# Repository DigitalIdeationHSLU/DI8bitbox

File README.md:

# DI 8bitbox

"DI 8bitbox" - Digital Ideation Musterplatine zum 140 jährigen Bestehen der HSLU

## What is inside this repository?

* PCB EagleCad Files + Gerber production Files
* Firmware (Arduino Code source)
* Shell script to zip Gerber Files
* CAM File for Itead Studio

## Assembly

### Bills of materials

You'll need following parts in order to finish your board.

* 2 x 100R 0805 SMD resistors
* 1 x 1k 0805 SMD resistor
* 1 x SOT23-3 NPN Transistor
* 2 x 1206 LEDs (preferably white, change resistor according to your colour)
* 1 x Atttiny 84 SMD Version
* 1 x Pogopin Sparkfun Connector ([Link](https://www.sparkfun.com/products/11591))
* 1 x optionally a tiny loudspeaker

You can find the exact details in this [BOM](https://github.com/DigitalIdeationHSLU/DI8bitbox/blob/master/documentation/Warenkorb_juin13_0443.xls) Excel sheet.

### Soldering

With little soldering skills, you should be able to finish the board. Please be careful when mounting the LEDs and the Attiny, since orientation is important. See mounting diagram:

## Install

### Flashing Firmware

Attach the Pogo-pin programmer to an Arduino or another AVR ISP-capable programming device. For the wiring see this photo:

Once in place, prepare your Arduino by adding the Attiny to the list of boards. Here's a [HOWTO](http://highlowtech.org/?p=1695).

Make sure the Arduino settings are correct by selecting "Arduino as ISP", the right Board "Attiny84", the right clock frequency "1Mhz" and the right USB port.

Press the Pogo pins gently onto the pads on the bottom side of the board. Again, orientation is important:

Hit the programming button within your Arduino sketch. You should see a succesful File upload in the terminal screen of the Arduino IDE.

### Final preparation

Attach 3-5 Volts DC to the input pins where you'll find the battery icon. Make sure polarity is correct according to +/- signs. Solder the tiny loudspeaker on the other side of the board. You should hear sound coming out immediately.

## Run

Download either this [Android app](https://play.google.com/store/apps/details?id=org.jfedor.morsecode) for capturing sound or the [Morse Talk](https://play.google.com/store/apps/details?id=com.blueta.morsetransmitter&hl=fr) and hold it above one of the LEDs. You should be able to decrypt the message.

## Credits

* Created by Gordan Savičić & Michael Schürmann, Luzern 2017

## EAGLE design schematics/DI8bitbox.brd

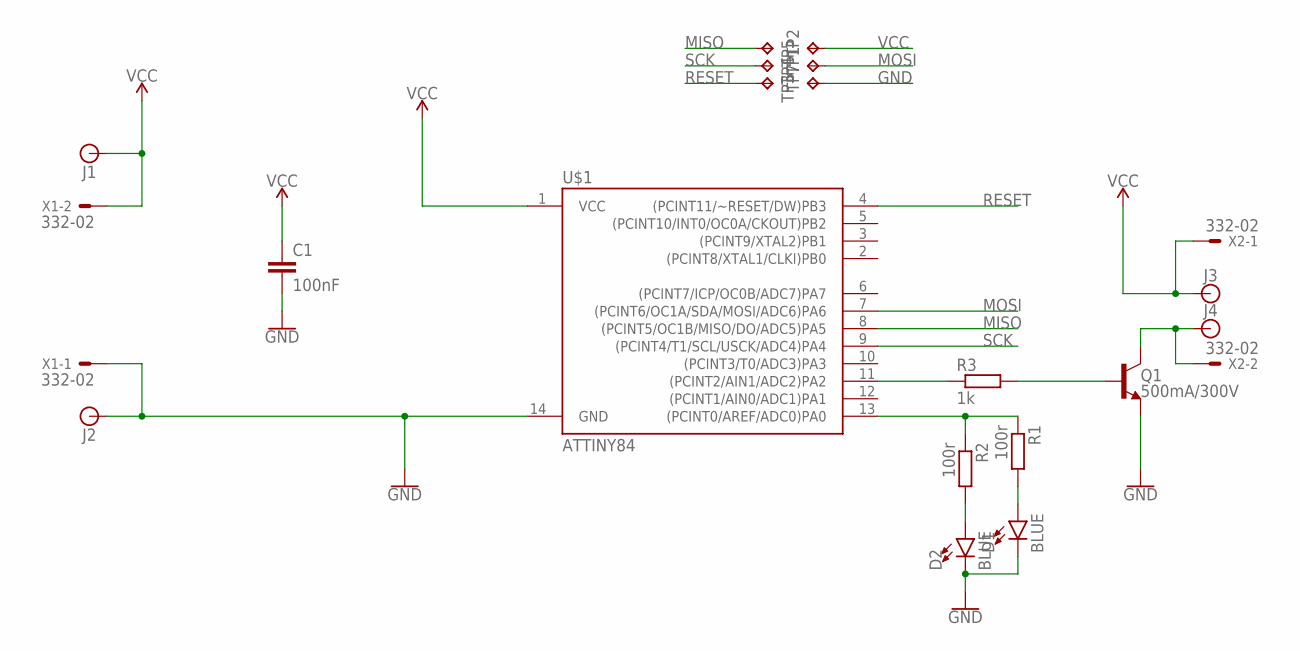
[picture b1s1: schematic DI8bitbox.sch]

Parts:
C1: 100nF; 1206
D1, D2: BLUE; LED-1206
J1, J2, J3, J4: BANANA_CONN
Q1: 500mA/300V; SOT23-3
R1, R2: 100r; M0805
R3: 1k; M0805
TP1, TP2, TP3, TP4, TP5, TP7: TPTP18R; TP18R
U$1: ATTINY84; SO14
X1, X2: 332-02

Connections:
GND: C1.2, D1.C, D2.C, J2.P$1, Q1.2 (E), TP7.TP, U$1.14 (GND), X1.1
MISO: TP5.TP, U$1.8 ((PCINT5/OC1B/MISO/DO/ADC5)PA5)
MOSI: TP1.TP, U$1.7 ((PCINT6/OC1A/SDA/MOSI/ADC6)PA6)
unnamed: R1.1, R2.1, U$1.13 ((PCINT0/AREF/ADC0)PA0)
unnamed: D2.A, R2.2
unnamed: D1.A, R1.2
unnamed: Q1.1 (B), R3.2
unnamed: R3.1, U$1.11 ((PCINT2/AIN1/ADC2)PA2)
RESET: TP3.TP, U$1.4 ((PCINT11/~RESET/DW)PB3)
SCK: TP4.TP, U$1.9 ((PCINT4/T1/SCL/USCK/ADC4)PA4)
SPK: J4.P$1, Q1.3 (C), X2.2
VCC: C1.1, J1.P$1, J3.P$1, TP2.TP, U$1.1 (VCC), X1.2, X2.1

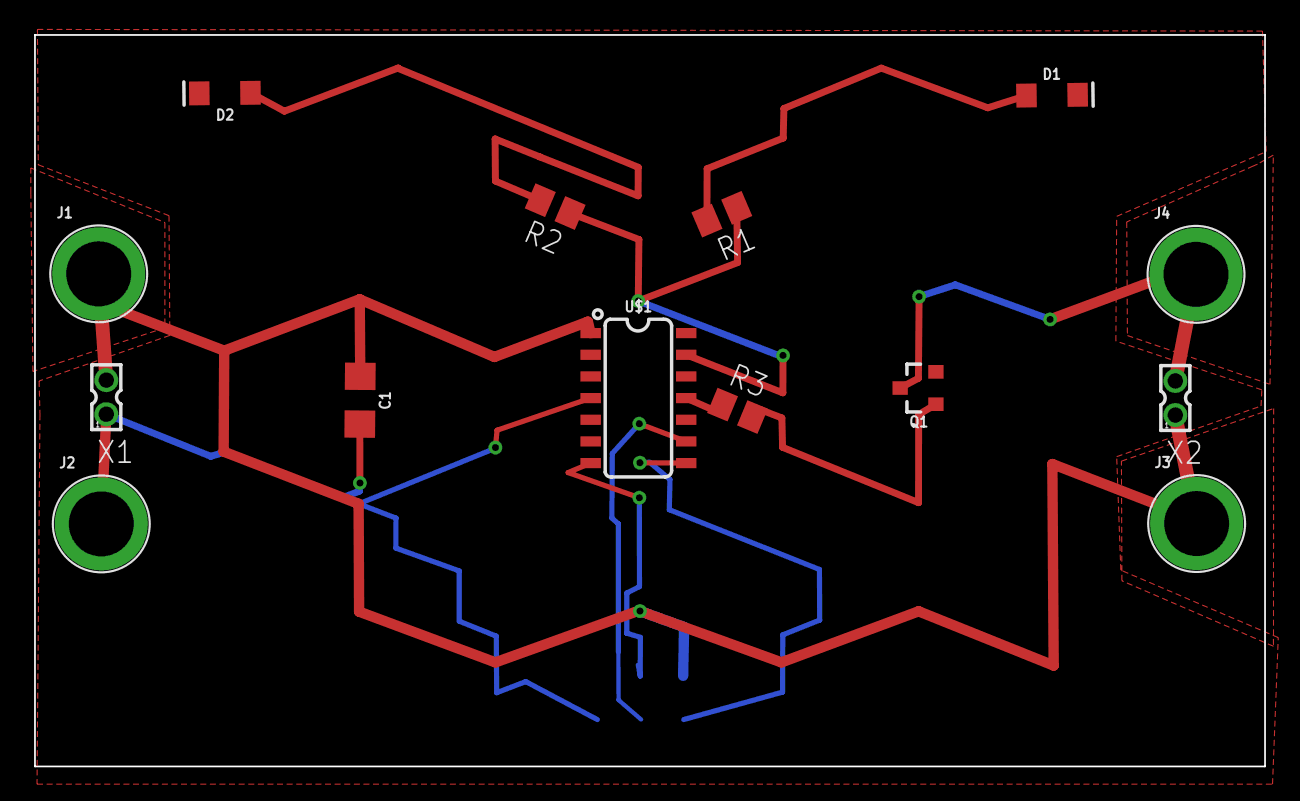
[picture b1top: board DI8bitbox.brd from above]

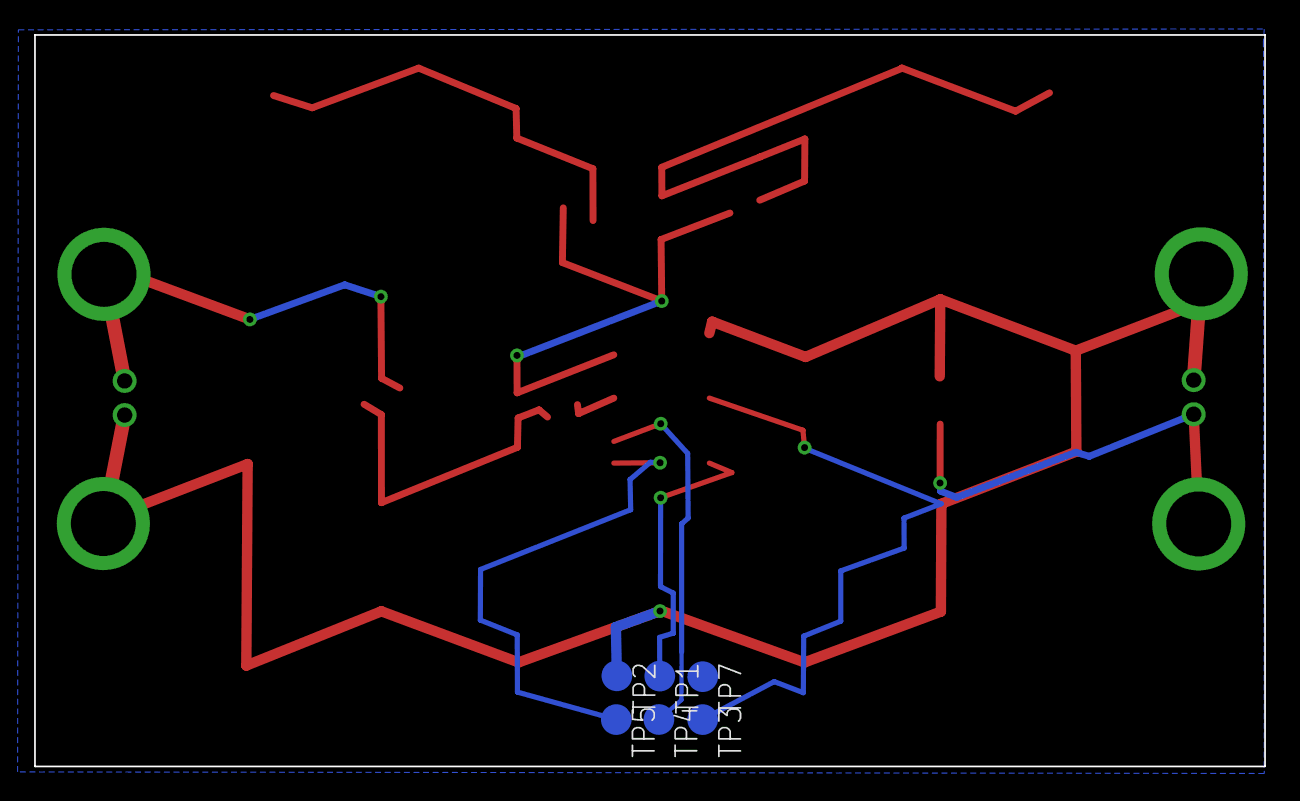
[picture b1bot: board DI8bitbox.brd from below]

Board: 2 copper layers, 72.1 x 42.9 mm, 20 parts (6 on the bottom side), 12 nets.

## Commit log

2017-03-23 README.md created online with Bitbucket
2017-03-26 added illustrator file
2017-03-30 no message
2017-04-12 added schematics and board design for morsecode with attiny84
2017-04-29 New Version. Size 42.828 mm x 72.125 mm
2017-04-29 NEW NEW NEEEEEEEEEEW :)
2017-04-29 this is it! only bitmap left..
2017-05-01 restored deleted brd files
2017-05-04 inserted silkscreen layer from Silkscreen.ai into eagle brd file + added screenshots for documentation
2017-05-05 cropped silkscreen mask
2017-05-05 Major changes in Illustrator design and first silkscreen experiments
2017-05-06 changed pads to polygon areas, added eagle up renderings, major re-design
2017-05-06 minor cleanups, first gerber files
2017-05-06 Ordered at Itead - rev.a finished
2017-05-08 added R3 to transistor base after itead prod
2017-05-08 added gerber files with R3
2017-06-13 ordered rev.b at safepcb and mouser BOM updated
2017-06-20 adding documentation
2017-06-21 removed ledpin2 from SimpleMorse
2017-07-04 updated simplemorse
2017-07-05 added hex files and troubleshoot

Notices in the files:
parts and their libraries:
SparkFun-Capacitors: Licensing: Creative Commons ShareAlike 4.0 International - https://creativecommons.org/licenses/by-sa/4.0
